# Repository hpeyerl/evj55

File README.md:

# Before

# Maybe

Files related to my EV conversion project.

## Related repos

- [evj55-dashboard](https://github.com/hpeyerl/evj55-dashboard) - dashboard firmware (Radxa CM3 + dual-CAN HAT+)
- [Wiring Harness](wiring/splice-cad-rendered/EVJ-55_plan_all_pages_schematic.pdf)

# Network system diagram

# Mechanical/Electrical system diagram

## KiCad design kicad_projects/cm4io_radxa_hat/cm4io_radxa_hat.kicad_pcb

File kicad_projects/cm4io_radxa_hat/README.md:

A HAT for a Raspberry Pi, in this case a CM4IO carrier with a RadXA CM3 module connected to a Waveshare 12.3 TOUCHA display, and a Waveshare dual CAN hat.  

Note:  The version pictured below has the RJ45 connector backwards.  This is fixed in the current version which has not been fabbed.

This board supports:

* RevUS Parking Brake controller status LED inputs.
* Up to 4 MagRide outputs for ride control (GM coils)
* GPS input
* Dual daisy-chained CAN (RJ-45)
* Center-Diff-Lock status input.
* HF2A Transfer case Lo-Range status input.
* HF2A transfer case VSS input.
* Dimmer status input (for day/night modes)

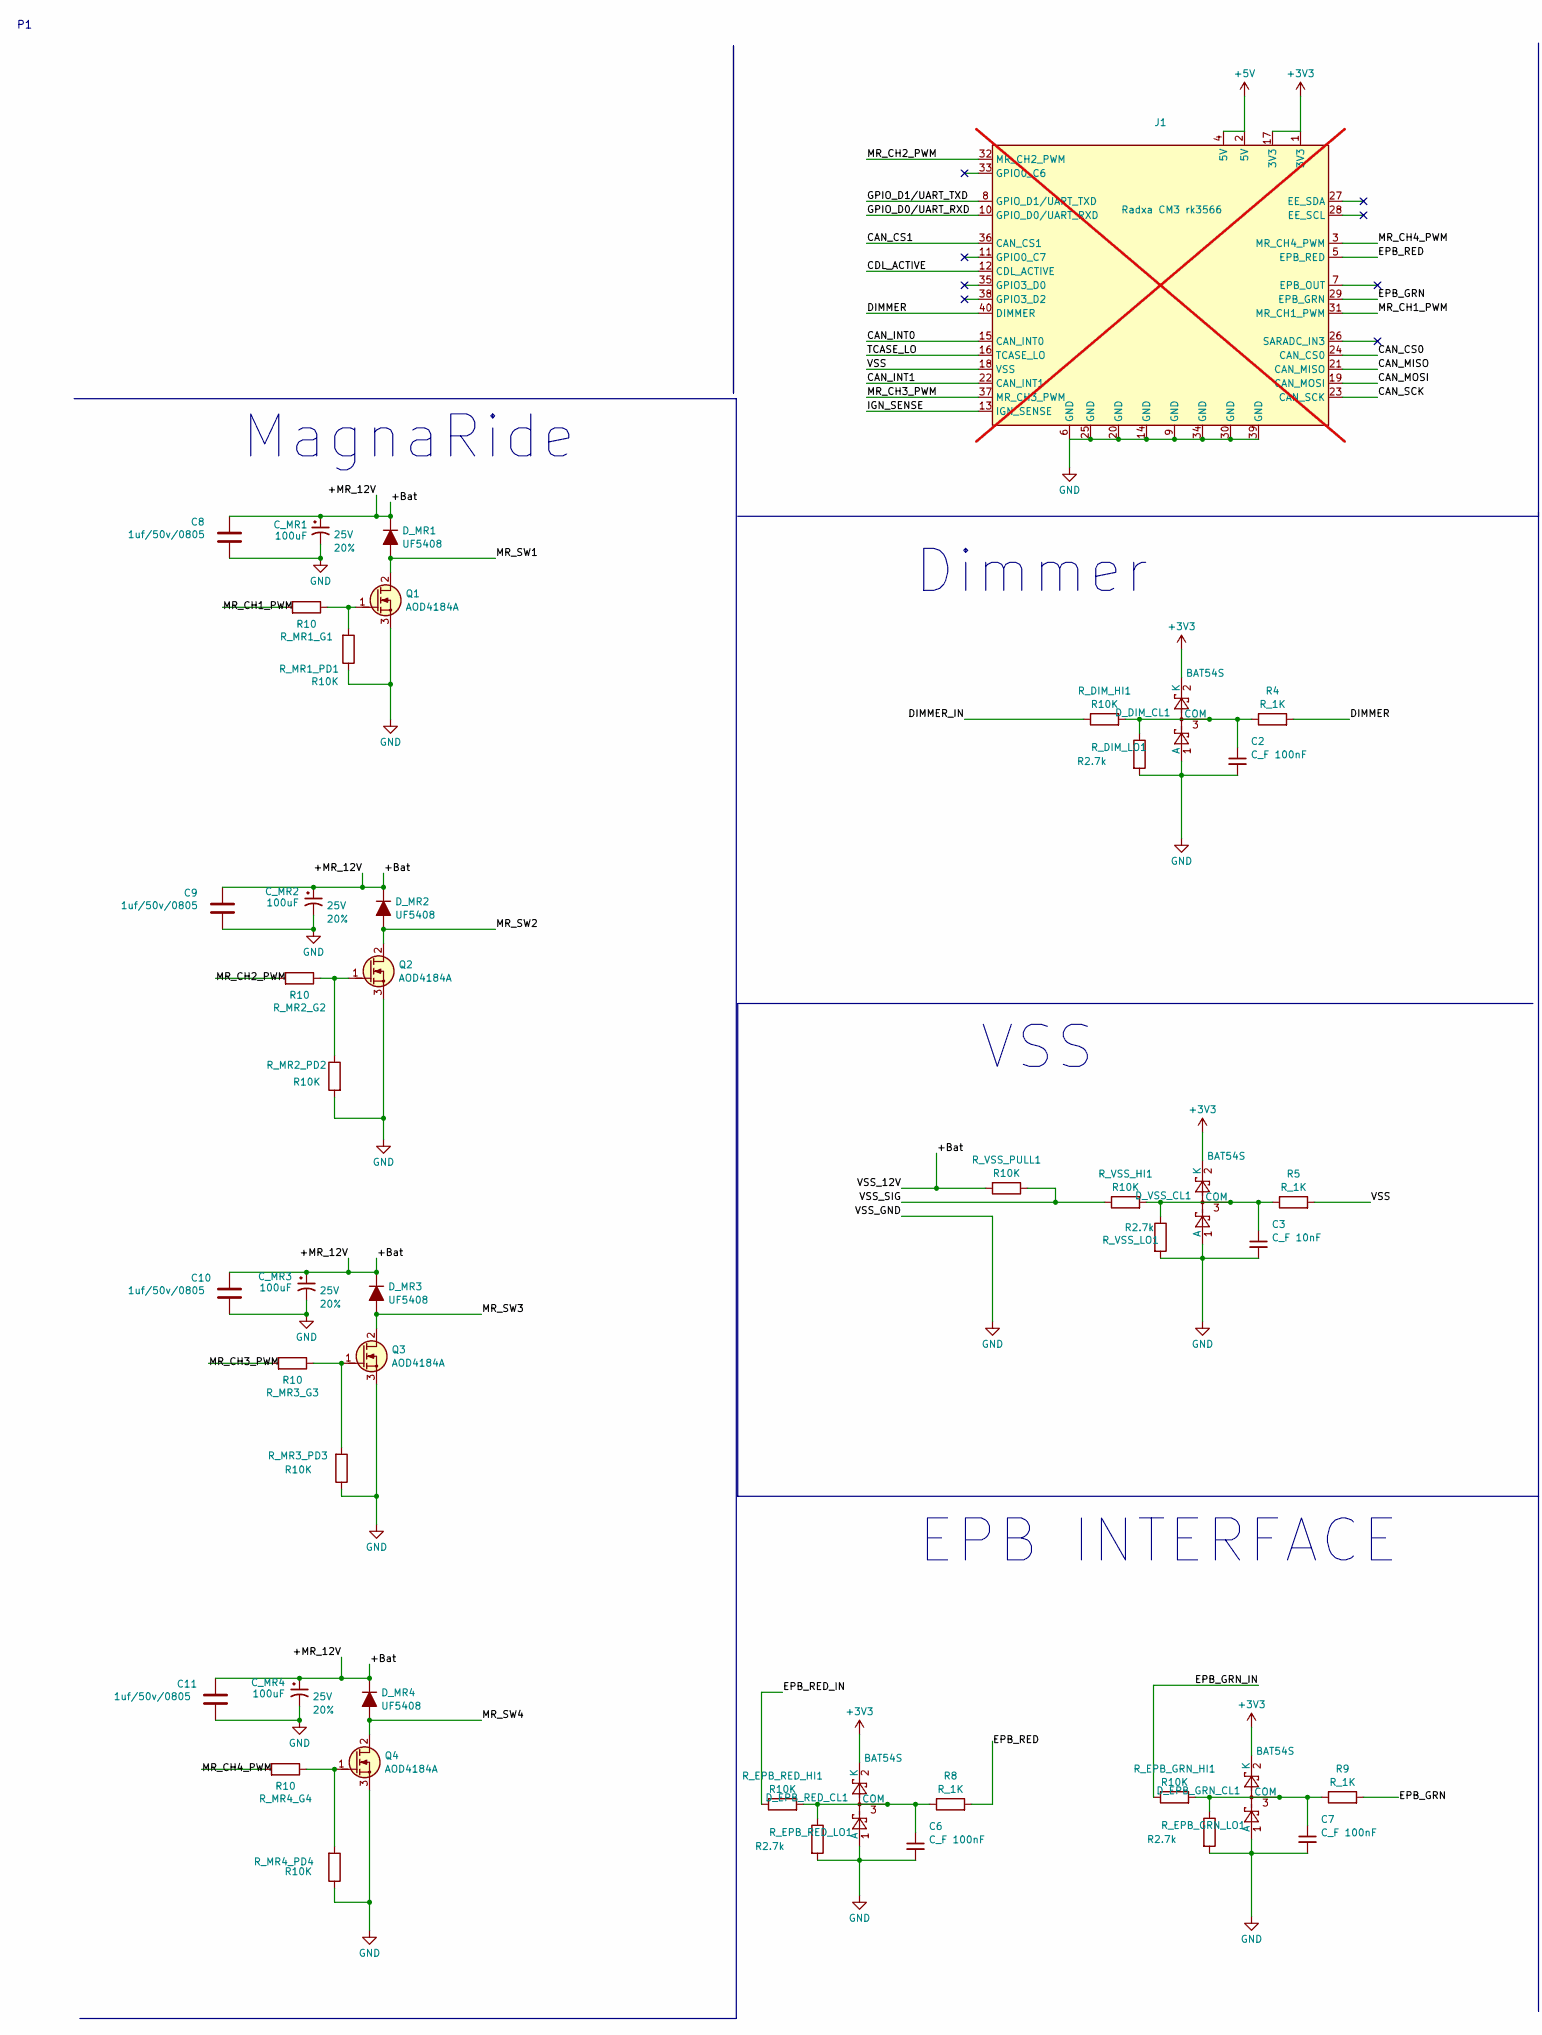
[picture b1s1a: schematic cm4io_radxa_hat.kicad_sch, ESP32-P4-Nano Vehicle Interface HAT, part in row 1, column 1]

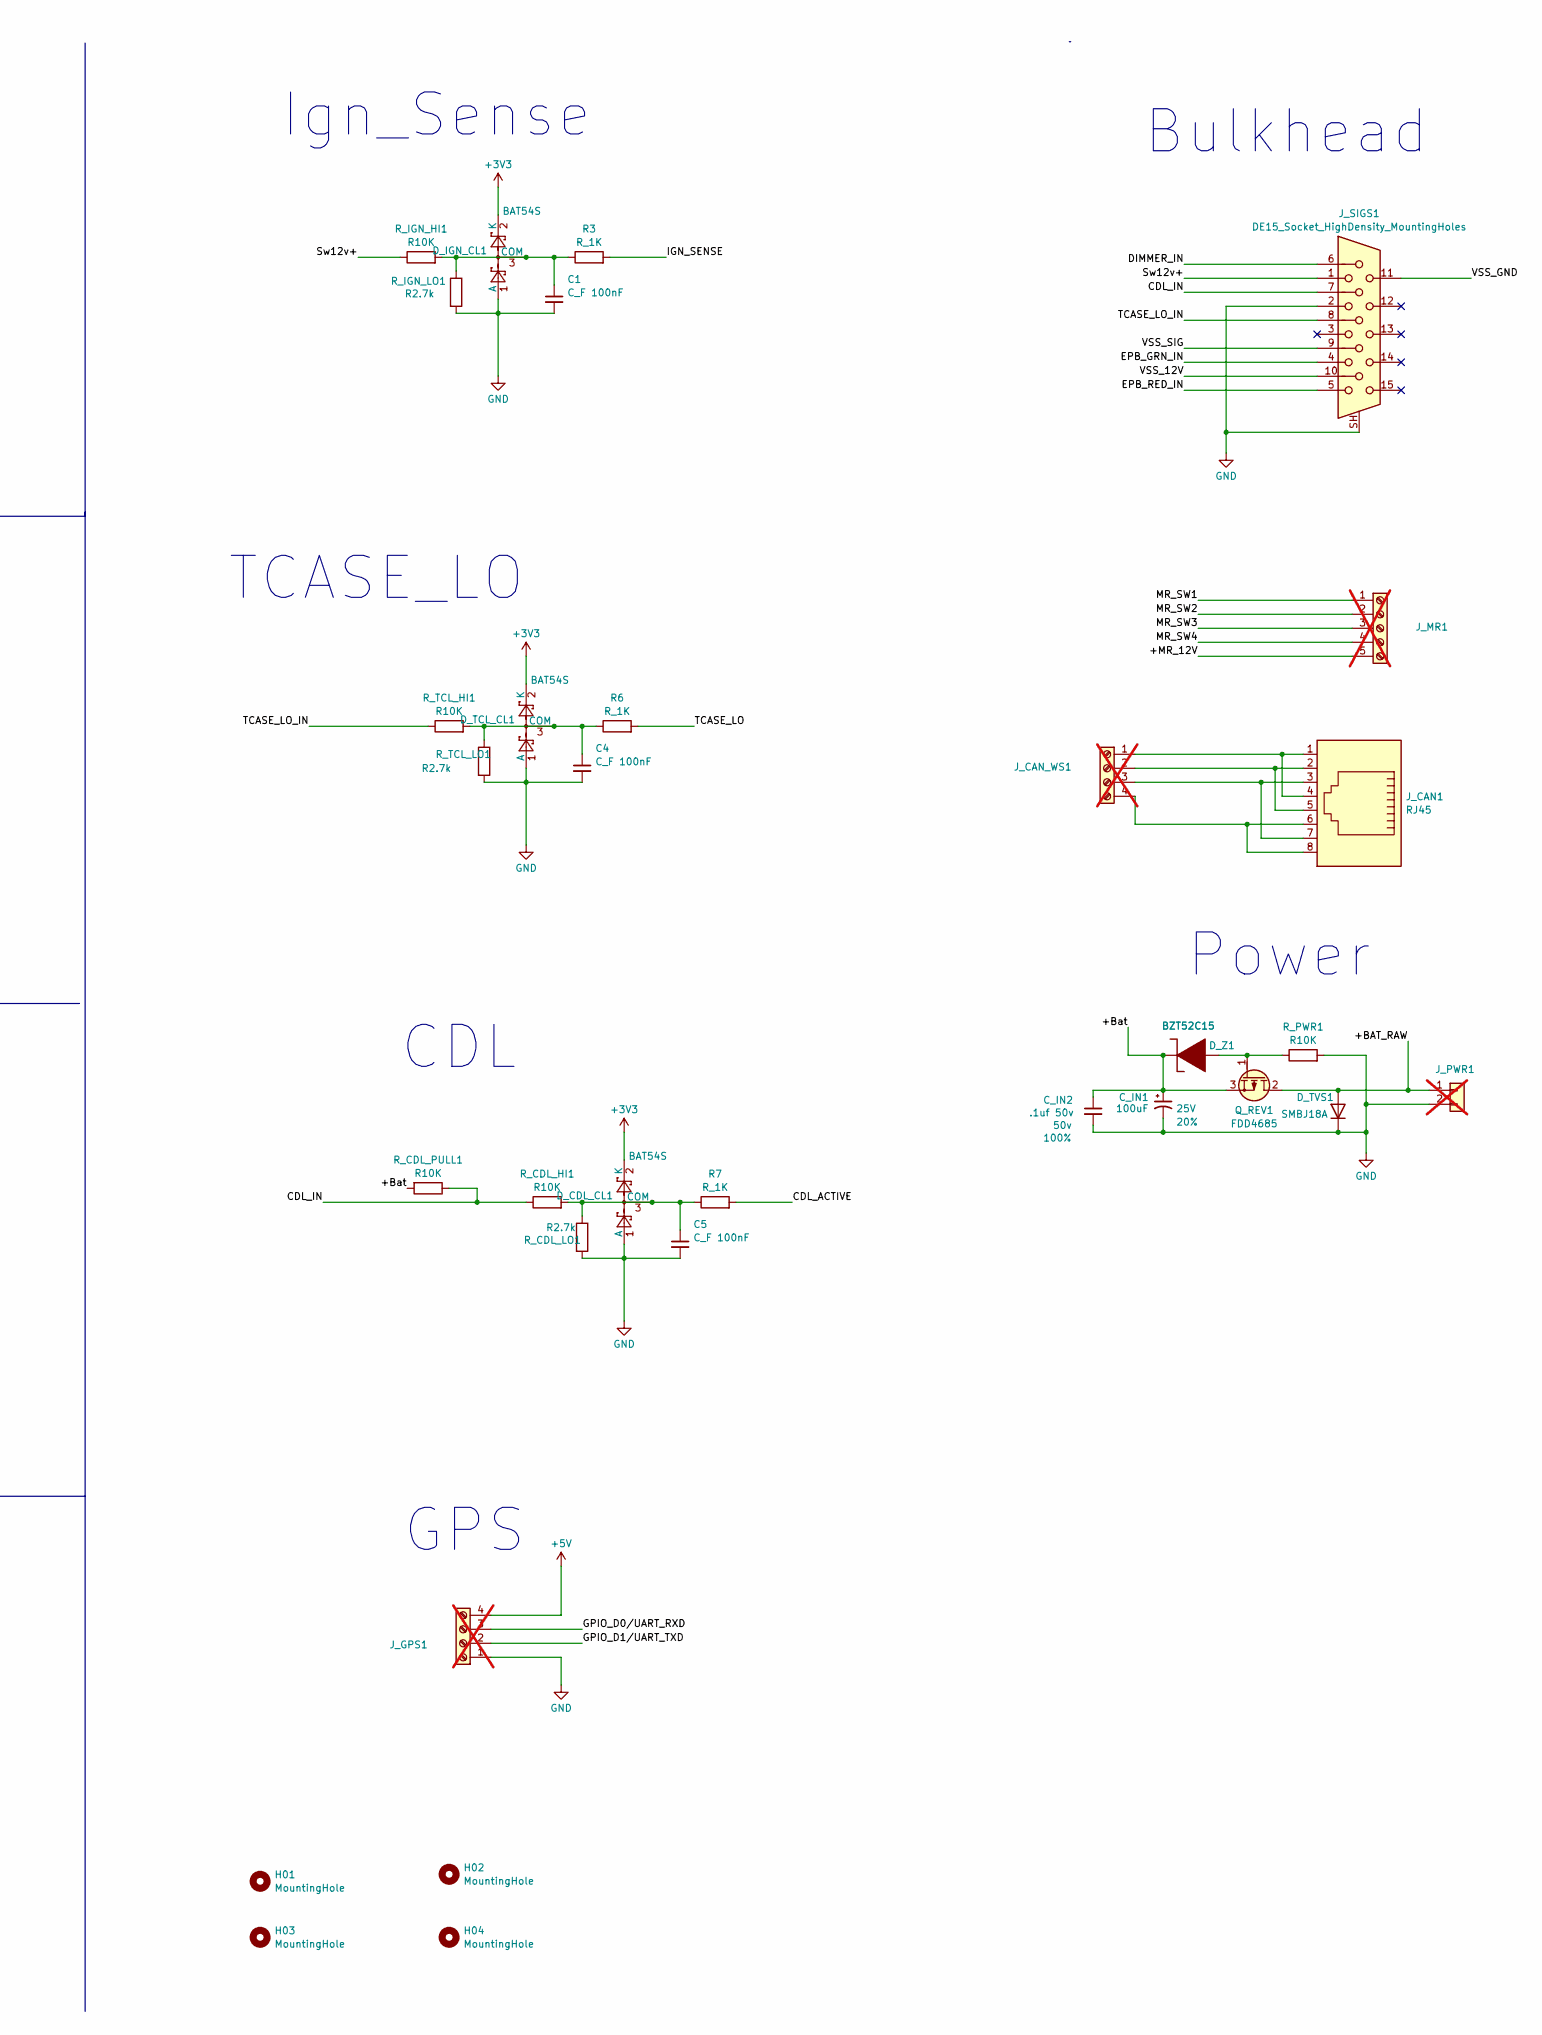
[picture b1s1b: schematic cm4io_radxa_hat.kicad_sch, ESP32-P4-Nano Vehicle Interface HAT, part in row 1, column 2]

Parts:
C1, C2, C4, C5, C6, C7: C_F 100nF; C_0402_1005Metric; Voltage 1kV; Tolerance 100%; LCSC C60474
C3: C_F 10nF; C_0402_1005Metric; Voltage 1kV; Tolerance 100%; LCSC C15195
C8, C9, C10, C11: 1uf/50v/0805; C_0805_2012Metric; LCSC C28323
C_IN1: 100uF; CP_Radial_D6.3mm_P2.50mm; Voltage 25V; Tolerance 20%; LCSC C2960218
C_IN2: .1uf 50v; C_0603_1608Metric; Voltage 50v; Tolerance 100%; LCSC C14663
C_MR1, C_MR2, C_MR3, C_MR4: 100uF; CP_Radial_D6.3mm_P2.50mm; Voltage 25V; Tolerance 20%; LCSC C2960218
D_CDL_CL1: BAT54S; SOT-23; LCSC C916425
D_DIM_CL1: BAT54S; SOT-23; LCSC C916425
D_EPB_GRN_CL1: BAT54S; SOT-23; LCSC C916425
D_EPB_RED_CL1: BAT54S; SOT-23; LCSC C916425
D_IGN_CL1: BAT54S; SOT-23; LCSC C916425
D_MR1, D_MR2, D_MR3, D_MR4: UF5408; D_DO-201AD_P5.08mm_Vertical_CathodeUp; LCSC C424502
D_TCL_CL1: BAT54S; SOT-23; LCSC C916425
D_TVS1: SMBJ18A; D_SMB_Handsoldering; LCSC C19077573
D_VSS_CL1: BAT54S; SOT-23; LCSC C916425
D_Z1: BZT52C15; D_SOD-123; LCSC C173427
H01, H02, H03, H04: MountingHole; MountingHole_2.5mm
J1: Radxa CM3 rk3566; IDC-Header_2x20_P2.54mm_Vertical; not fitted
J_CAN1: RJ45; RJ45_Amphenol_RJHSE5380; LCSC C464586
J_CAN_WS1: rr; TerminalBlock_Phoenix_PT-1,5-4-3.5-H_1x04_P3.50mm_Horizontal; not fitted
J_GPS1: Screw_Terminal_01x04; TerminalBlock_Phoenix_PT-1,5-4-3.5-H_1x04_P3.50mm_Horizontal; not fitted
J_MR1: Screw_Terminal_01x05; TerminalBlock_Phoenix_PT-1,5-5-3.5-H_1x05_P3.50mm_Horizontal; not fitted
J_PWR1: Screw_Terminal_01x02; TerminalBlock_Phoenix_PT-1,5-2-3.5-H_1x02_P3.50mm_Horizontal; not fitted
J_SIGS1: DE15_Socket_HighDensity_MountingHoles; DSUB-15-HD_Socket_Horizontal_P2.29x1.90mm_EdgePinOffset3.03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; LCSC C711364
Q1, Q2, Q3, Q4: AOD4184A; TO-252-2; LCSC C99124
Q_REV1: FDD4685; TO-252-2; LCSC C258227
R3, R4, R5, R6, R7, R8, R9: R_1K; R_0402_1005Metric; LCSC C2906864
R_CDL_HI1: R10K; R_0402_1005Metric; LCSC C25744
R_CDL_LO1: R2.7k; R_0402_1005Metric; LCSC C2909332
R_CDL_PULL1: R10K; R_0402_1005Metric; LCSC C25744
R_DIM_HI1: R10K; R_0402_1005Metric; LCSC C25744
R_DIM_LO1: R2.7k; R_0402_1005Metric; LCSC C2909332
R_EPB_GRN_HI1: R10K; R_0402_1005Metric; LCSC C25744
R_EPB_GRN_LO1: R2.7k; R_0402_1005Metric; LCSC C2909332
R_EPB_RED_HI1: R10K; R_0402_1005Metric; LCSC C25744
R_EPB_RED_LO1: R2.7k; R_0402_1005Metric; LCSC C2909332
R_IGN_HI1: R10K; R_0402_1005Metric; LCSC C25744
R_IGN_LO1: R2.7k; R_0402_1005Metric; LCSC C2909332
R_MR1_G1, R_MR2_G2, R_MR3_G3, R_MR4_G4: R10; R_0402_1005Metric; LCSC C138066
R_MR1_PD1, R_MR2_PD2, R_MR3_PD3, R_MR4_PD4: R10K; R_0402_1005Metric; LCSC C25744
R_PWR1: R10K; R_0402_1005Metric; LCSC C25744
R_TCL_HI1: R10K; R_0402_1005Metric; LCSC C25744
R_TCL_LO1: R2.7k; R_0402_1005Metric; LCSC C2909332
R_VSS_HI1: R10K; R_0402_1005Metric; LCSC C25744
R_VSS_LO1: R2.7k; R_0402_1005Metric; LCSC C2909332
R_VSS_PULL1: R10K; R_0402_1005Metric; LCSC C25744

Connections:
+3V3: D_CDL_CL1.2 (K), D_DIM_CL1.2 (K), D_EPB_GRN_CL1.2 (K), D_EPB_RED_CL1.2 (K), D_IGN_CL1.2 (K), D_TCL_CL1.2 (K), D_VSS_CL1.2 (K), J1.1 (3V3), J1.17 (3V3)
+5V: J1.2 (5V), J1.4 (5V), J_GPS1.4
/+BAT_RAW: D_TVS1.2 (A), J_PWR1.1, Q_REV1.2 (D)
/+Bat: C8.1, C9.1, C10.1, C11.1, C_IN1.1, C_IN2.1, C_MR1.1, C_MR2.1, C_MR3.1, C_MR4.1, D_MR1.1 (K), D_MR2.1 (K), D_MR3.1 (K), D_MR4.1 (K), D_Z1.1 (K-), J_MR1.5, J_SIGS1.10, Q_REV1.3 (S), R_CDL_PULL1.2, R_VSS_PULL1.2
/CAN_CS0: J1.24 (CAN_CS0)
/CAN_CS1: J1.36 (CAN_CS1)
/CAN_INT0: J1.15 (CAN_INT0)
/CAN_INT1: J1.22 (CAN_INT1)
/CAN_MISO: J1.21 (CAN_MISO)
/CAN_MOSI: J1.19 (CAN_MOSI)
/CAN_SCK: J1.23 (CAN_SCK)
/CDL_ACTIVE: J1.12 (CDL_ACTIVE), R7.2
/CDL_IN: J_SIGS1.7, R_CDL_HI1.1, R_CDL_PULL1.1
/DIMMER: J1.40 (DIMMER), R4.2
/DIMMER_IN: J_SIGS1.6, R_DIM_HI1.1
/EPB_GRN: J1.29 (EPB_GRN), R9.2
/EPB_GRN_IN: J_SIGS1.4, R_EPB_GRN_HI1.1
/EPB_RED: J1.5 (EPB_RED), R8.2
/EPB_RED_IN: J_SIGS1.5, R_EPB_RED_HI1.1
/GPIO_D0/UART_RXD: J1.10 (GPIO_D0/UART_RXD), J_GPS1.3
/GPIO_D1/UART_TXD: J1.8 (GPIO_D1/UART_TXD), J_GPS1.2
/IGN_SENSE: J1.13 (IGN_SENSE), R3.2
/MR_CH1_PWM: J1.31 (MR_CH1_PWM), R_MR1_G1.1
/MR_CH2_PWM: J1.32 (MR_CH2_PWM), R_MR2_G2.1
/MR_CH3_PWM: J1.37 (MR_CH3_PWM), R_MR3_G3.1
/MR_CH4_PWM: J1.3 (MR_CH4_PWM), R_MR4_G4.1
/MR_SW1: D_MR1.2 (A), J_MR1.1, Q1.2 (D)
/MR_SW2: D_MR2.2 (A), J_MR1.2, Q2.2 (D)
/MR_SW3: D_MR3.2 (A), J_MR1.3, Q3.2 (D)
/MR_SW4: D_MR4.2 (A), J_MR1.4, Q4.2 (D)
/Sw12v+: J_SIGS1.1, R_IGN_HI1.1
/TCASE_LO: J1.16 (TCASE_LO), R6.2
/TCASE_LO_IN: J_SIGS1.8, R_TCL_HI1.1
/VSS: J1.18 (VSS), R5.2
/VSS_SIG: J_SIGS1.9, R_VSS_HI1.1, R_VSS_PULL1.1
GND: C1.2, C2.2, C3.2, C4.2, C5.2, C6.2, C7.2, C8.2, C9.2, C10.2, C11.2, C_IN1.2, C_IN2.2, C_MR1.2, C_MR2.2, C_MR3.2, C_MR4.2, D_CDL_CL1.1 (A), D_DIM_CL1.1 (A), D_EPB_GRN_CL1.1 (A), D_EPB_RED_CL1.1 (A), D_IGN_CL1.1 (A), D_TCL_CL1.1 (A), D_TVS1.1 (K), D_VSS_CL1.1 (A), J1.6 (GND), J1.9 (GND), J1.14 (GND), J1.20 (GND), J1.25 (GND), J1.30 (GND), J1.34 (GND), J1.39 (GND), J_GPS1.1, J_PWR1.2, J_SIGS1.2, J_SIGS1.11, J_SIGS1.SH, Q1.3 (S), Q2.3 (S), Q3.3 (S), Q4.3 (S), R_CDL_LO1.2, R_DIM_LO1.2, R_EPB_GRN_LO1.2, R_EPB_RED_LO1.2, R_IGN_LO1.2, R_MR1_PD1.2, R_MR2_PD2.1, R_MR3_PD3.2, R_MR4_PD4.2, R_PWR1.1, R_TCL_LO1.2, R_VSS_LO1.2
unnamed: C5.1, D_CDL_CL1.3 (COM), R7.1, R_CDL_HI1.2, R_CDL_LO1.1
unnamed: C2.1, D_DIM_CL1.3 (COM), R4.1, R_DIM_HI1.2, R_DIM_LO1.1
unnamed: C7.1, D_EPB_GRN_CL1.3 (COM), R9.1, R_EPB_GRN_HI1.2, R_EPB_GRN_LO1.1
unnamed: C6.1, D_EPB_RED_CL1.3 (COM), R8.1, R_EPB_RED_HI1.2, R_EPB_RED_LO1.1
unnamed: C1.1, D_IGN_CL1.3 (COM), R3.1, R_IGN_HI1.2, R_IGN_LO1.1
unnamed: C4.1, D_TCL_CL1.3 (COM), R6.1, R_TCL_HI1.2, R_TCL_LO1.1
unnamed: C3.1, D_VSS_CL1.3 (COM), R5.1, R_VSS_HI1.2, R_VSS_LO1.1
unnamed: D_Z1.2 (A+), Q_REV1.1 (G), R_PWR1.2
unnamed: J_CAN1.1, J_CAN1.4, J_CAN_WS1.1
unnamed: J_CAN1.2, J_CAN1.5, J_CAN_WS1.2
unnamed: J_CAN1.3, J_CAN1.7, J_CAN_WS1.3
unnamed: J_CAN1.6, J_CAN1.8, J_CAN_WS1.4
unnamed: Q1.1 (G), R_MR1_G1.2, R_MR1_PD1.1
unnamed: Q2.1 (G), R_MR2_G2.2, R_MR2_PD2.2
unnamed: Q3.1 (G), R_MR3_G3.2, R_MR3_PD3.1
unnamed: Q4.1 (G), R_MR4_G4.2, R_MR4_PD4.1

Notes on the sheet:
EPB INTERFACE
TCASE_LO
VSS
MagnaRide
GPS
CDL
Power
Bulkhead
Dimmer
Ign_Sense

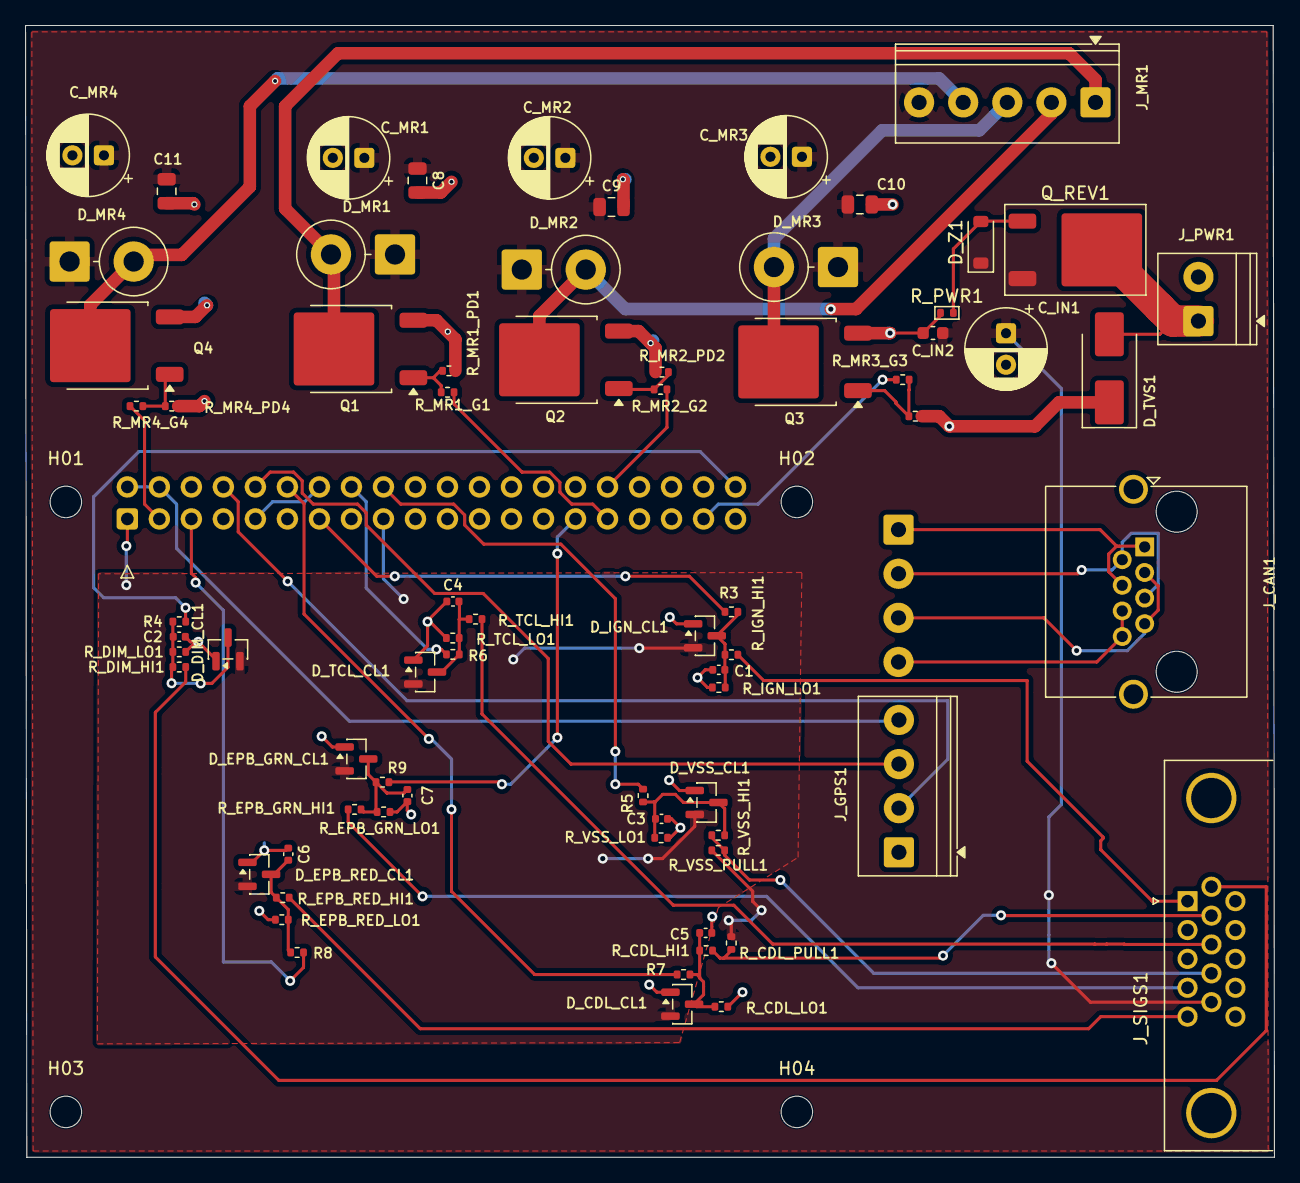
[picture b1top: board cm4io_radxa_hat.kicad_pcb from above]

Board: 2 copper layers, 99.1 x 89.8 mm, 78 parts (1 on the bottom side), 45 nets.

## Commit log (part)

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2025-05-06 Play with Wireviz
2025-05-06 Start documenting
2025-05-07 Workaround lack of include feature in yaml by using cpp
2025-05-07 latest output file
2025-05-07 fix pin names on BMW throttle pedal
2025-05-09 Need to build the harnesses as modules. It will be too unwieldy to have one single harness schematic
2025-05-09 pin changes from @robertwa
2025-05-09 colorize the inverter/resolver cables
2025-05-09 Start documenting our HF1A tcase wiring
2025-05-13 clean up include dependencies
2025-05-13 add some connector images. Wire up the oil pump connector
2025-05-15 Need a README to add some words to this
2025-05-15 Switch to Honda Fit pedal
2025-05-15 start incorporating notes from old FJ55LV wiring diagrams
2025-05-15 image for honda_fit_pedal_connector from openinverter wiki
2025-05-16 pinlabels were reversed between mg1/mg2
2025-05-16 fix some errors after review. Document the shields on the resolver cables
2025-05-16 move zombie stuff to its own repo and create submodule for it here
2025-09-14 HF1A tcase is actually an HF2A
2025-12-15 update submodule
2025-12-25 remove some connector images that are in the zombie repo
2025-12-25 play with wireviz-web
2025-12-26 update per 93 FZJ80 FSM schematic p5
2026-01-03 Add wiring for ibooster GEN1 from Honda CRV 2019
2026-01-03 Housekeeping
2026-01-26 Images for fuses, milround and transmission control relay
2026-01-26 don't ignore png's
2026-01-30 Create a README?
2026-01-30 L110F stuff
2026-01-30 Rename
2026-01-30 HF2A-L110F adapter. V4 and not yet cut
2026-01-30 Oil pump adapter. V2. This was the version milled at jlccnc
2026-01-30 Describe each file a bit
2026-01-30 emphasize file names
2026-02-02 Parts that differ from stock
2026-02-02 another couple parts
2026-02-02 Add a tantalizing image
2026-02-03 switch to better color
2026-02-04 before and after
2026-02-04 updates to README
2026-02-06 Remove O-ring bosses because they prevent sealing of the cavity next to the ports causing leaks.
2026-04-15 Move Wireviz stuff to its own dir. Import current wiring plan from SpliceCad
2026-04-16 A git action to hopefully render my Splice-Cad wiring harness
2026-04-16 chore: update rendered wiring outputs [skip ci]
2026-04-16 more changes
2026-04-18 Update wiring/EVJ-55_plan.json via splice
2026-04-18 Update splice.yml via splice
2026-04-20 Update render workflow via splice
2026-04-20 chore: update rendered outputs [skip ci]
2026-05-19 System Diagram WIP
2026-06-07 updated system diagram and document scope creep under consideration
2026-06-07 a mechanical system diagram
2026-06-07 cleanup system diagrams a bit
